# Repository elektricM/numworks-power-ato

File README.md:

# NumWorks N0100 Power Module

Custom power management board for running a Raspberry Pi Zero 2W inside a NumWorks N0100 calculator.

## Why This Exists

The [numworks-rpi](https://github.com/elektricM/numworks-rpi) project replaces the internals of a NumWorks calculator with a Raspberry Pi Zero 2W running Linux. This requires a custom power solution that can:
- ✅ Charge the Li-Ion battery (replacing the failed RT9526A charger)
- ✅ Protect the battery (overcurrent, overvoltage, undervoltage)
- ✅ Provide stable 5V power for the Raspberry Pi from a 3.7V battery
- ✅ Fit within the calculator's tight space constraints (38x24mm max)

This board does all of that in a single custom PCB.

## What It Does

**Three integrated circuits on one compact board:**

### 1. TP4056 Li-Ion Charger
Replaces the dead RT9526A charger on the original calculator. Standard 1A charge current with automatic termination.

### 2. DW01A + FS8205A Battery Protection
Complete protection circuitry:
- Overcurrent protection (discharge > 3A, charge > 1.5A)
- Overvoltage protection (> 4.25V)
- Undervoltage protection (< 2.4V)
- Auto-recovery when fault conditions clear

### 3. TPS63020 Buck-Boost Converter
Maintains stable 5V output for the Raspberry Pi across the full battery voltage range (3.0V - 4.2V):
- 95% efficiency typical
- Up to 2A output current
- Seamless transition between buck and boost modes

## Why atopile?

This board is designed with [atopile](https://atopile.io), a modern code-first PCB design tool, instead of traditional KiCad or Altium.

**Benefits:**
- 📝 **Version control friendly** — Circuit described in plain text, easy to diff and review
- 🔍 **Automatic part sourcing** — Searches JLCPCB/LCSC inventory for available parts
- 🔄 **Parametric components** — Easy to swap parts while maintaining electrical compatibility
- 🧪 **Design validation** — Catch errors before layout with built-in checking

All components are sourced from JLCPCB/LCSC for straightforward assembly and low-cost manufacturing.

## Component Selection

| Component | Part Number | Why This One |
|-----------|-------------|--------------|
| Charger IC | TP4056 | Ubiquitous, cheap (~$0.10), proven reliability, 1A charge current matches original |
| Protection IC | DW01A | Industry standard battery protection IC, tiny SOT-23-6 package |
| Protection MOSFETs | FS8205A | Dual N-channel MOSFETs in SOT-23-6, perfectly matched for DW01A |
| Buck-Boost | TPS63020 | Can operate in buck OR boost mode, 95% efficiency, up to 2A output, small footprint |

Full design rationale and power budget analysis available in [docs/design-spec.md](docs/design-spec.md).

## Board Specifications

- **Dimensions:** 38mm × 24mm (fits NumWorks internal space)
- **Input voltage:** USB 5V (charging) or battery 3.0V-4.2V (operation)
- **Output voltage:** 5.0V ± 2% (for Raspberry Pi)
- **Maximum output current:** 2A continuous (sufficient for RPi Zero 2W)
- **Charge current:** 1A (programmable via resistor)
- **Layers:** 2-layer PCB
- **Manufacturing:** Designed for JLCPCB assembly

## Status

✅ **Tested and working** — Successfully integrated into the numworks-rpi project. Powers the Raspberry Pi Zero 2W reliably with good battery life.

## Building

Requires [atopile](https://atopile.io) v0.14.0 or newer.

```bash
# Install atopile
pip install atopile

# Build the design
ato build

# Output files will be in build/
```

The build generates:
- Netlist (JSON)
- Schematic (SVG)
- Layout files for manufacturing

## Related Projects

- **[numworks-rpi](https://github.com/elektricM/numworks-rpi)** — Main project: Raspberry Pi Zero 2W running Linux inside a NumWorks calculator
- **[numworks-power-pcb](https://github.com/elektricM/numworks-power-pcb)** — Earlier KiCad-based version of this board (deprecated)

## Documentation

- **[Design Spec](docs/design-spec.md)** — Complete circuit design, pin mappings, component selection rationale, and power budget calculations
- **[Tool Learnings](docs/tool-learnings.md)** — Comparison of PCB design tools: atopile vs traditional EDA

## Project Structure

```
numworks-power-ato/
├── ato.yaml              # atopile project configuration
├── main.ato              # Top-level circuit definition
├── parts/                # Component library (charger, protection, buck-boost)
├── layouts/              # PCB layout definitions
├── docs/                 # Design documentation
│   ├── design-spec.md    # Circuit design and analysis
│   └── tool-learnings.md # PCB tool comparison
├── schematic.svg         # Generated schematic image
└── *.py                  # Build and layout automation scripts
```

## Manufacturing

This board is designed for JLCPCB's PCB assembly service:
1. Export Gerber files from atopile build output
2. Upload to JLCPCB
3. All components are in JLCPCB's parts library
4. SMT assembly is straightforward with BOM and pick-place files

## License

MIT License — see [LICENSE.txt](LICENSE.txt) for details.

---

**Part of the [numworks-rpi](https://github.com/elektricM/numworks-rpi) project**

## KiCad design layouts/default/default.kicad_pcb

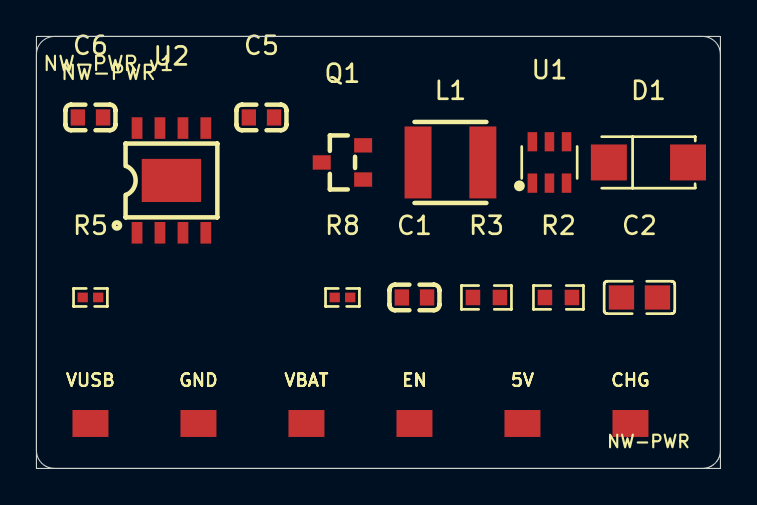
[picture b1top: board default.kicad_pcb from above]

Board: 2 copper layers, 38.0 x 24.0 mm, 19 parts (0 on the bottom side), 10 nets, no tracks yet.

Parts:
C1, C5, C6: 0F; C0603
C2: 0F; C0805
D1: SMA_L4.3-W2.6-LS5.2-RD
J1, J2, J3, J4, J5, J6: SolderPad
L1: IND-SMD_L4.0-W4.0_LQH44PN2R2MP0L
Q1: SOT-23_L2.9-W1.3-P1.90-LS2.4-BR
R2: 30000Ω; R0603
R3: 220000Ω; R0603
R5: 2000Ω; R0402
R8: 100000Ω; R0402
U1: SOT-23-6_L2.9-W1.6-P0.95-LS2.8-BL
U2: ESOP-8_L4.9-W3.9-P1.27-LS6.0-BL-EP

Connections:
2: D1.2, L1.2, U1.1
FB: R2.1, R3.2, U1.3
PROG: R5.1, U2.2
c_bat-power-hv: C5.1, J5.1, Q1.2, R8.1, U2.5
c_in-power-hv: C6.1, J6.1, U2.4, U2.8
c_out-power-hv: C2.1, D1.1, J4.1, R3.1
chg_stat: J1.1, U2.7
hv: C1.1, L1.1, Q1.3, U1.4, U1.5
lv: C1.2, C2.2, C5.2, C6.2, J2.1, R2.2, R5.2, U1.2, U2.1, U2.3, U2.9
pi_en: J3.1, Q1.1, R8.2

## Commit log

2026-02-02 NumWorks N0100 power module - atopile build (TP4056 + DW01A + TPS63020)
2026-02-02 Upgrade to atopile v0.14.0 (Python 3.14), fix pin names
2026-02-02 Rearrange PCB layout: group by functional block (buck-boost/charger/protection/monitor), add 39.5x16.5mm board outline
2026-02-02 Clean slate: remove old PCB code, keep docs (design spec + tool learnings)
2026-02-02 Fresh build: TP4056 charger + DW01A/FS8205A protection + TPS63020 buck-boost, layout grouped by block (39x17mm)
2026-02-02 Simplify: remove battery protection, add AO3401A P-MOSFET power switch for Pi (35x15mm, 19 components)
2026-02-02 Remove battery monitor (mainboard handles it), 16 components on 32x15mm
    Firmware confirmed: zardam's rpi.h uses PB9 P-channel MOSFET
    - PowerPin(GPIOB, 9), drive low = on, float = off
    - Matches our AO3401A + 100k pull-up circuit exactly
2026-02-02 Replace TPS63020 with SX1308 boost converter
    - SX1308 (C78162): SOT-23-6, 2A output, hand-solderable
    - Added SS34 Schottky diode (C8678) for async boost rectification
    - Simplified MOSFET gate: removed unnecessary R_gate to GND, keep only 100kΩ pull-up
    - Removed TPS63020 (VSON-14 pads too small for hand soldering)
    - Feedback divider: 220kΩ/30kΩ → 5.0V output
    - BOM reduced from 16 to 12 components
2026-02-02 Optimize JLCPCB cost: use 0603 feedback resistors (Basic parts)
    30kΩ and 220kΩ are Extended in 0402 but Basic in 0603.
    Saves $6 in extended part fees (from $15 to $9).
2026-02-02 Use compact 4x4x2mm inductor (SMNR4020-22UH)
    Replaced bulky 7.3x6.6x3mm inductor with 4x4x2mm shielded version.
    Same 22µH value, 1.05A rated - sufficient for Pi Zero 2W load.
    Max component height now 2.1mm (SS34 Schottky diode).
2026-02-02 Add PCB layout: 6 solder pads, component placement, routing, ground pour
    - Created SolderPad component (2x1.5mm SMD pads) for 6 wire connections
    - Board outline: 30x18mm with rounded corners
    - 3-zone layout: charger (left) → MOSFET (center) → boost (right)
    - Solder pads along bottom edge: VUSB, GND, VBAT, PI_EN, V5_PI, CHG
    - 50 trace segments, 11 vias, GND pour on B.Cu
    - Power traces 0.5mm, signal traces 0.25mm
2026-02-02 Fix layout: proper pad spacing, clean placement, remove bad routing
    - 6 solder pads evenly spaced along bottom edge (4.8mm apart)
    - Components grouped: charger left, MOSFET center, boost right
    - Removed all programmatic traces/vias/zones - route in KiCad
    - Clean silkscreen labels (VUSB, GND, VBAT, EN, 5V, CHG)
    - 30x18mm board outline
2026-02-02 Add schematic diagram SVG
2026-02-02 Regenerate schematic from atopile graph data (verified netlist)
2026-02-02 Proper schematic via netlistsvg (Yosys JSON netlist)
2026-02-02 Clean schematic: fix cell names, no duplicates
2026-02-02 Fix all 6 solder pad positions (were stacked, now spaced)
2026-02-02 Layout v2: proper spacing, 38x24mm board, GND pour, no overlaps
    - Components spaced by actual footprint size
    - 3 zones: charger (left) | MOSFET (center) | boost (right)
    - Row 1 (y=87): ICs, inductor, diode
    - Row 2 (y=95): small passives
    - Row 3 (y=101.5): 6 solder pads, 6mm apart
    - GND copper pour on B.Cu
2026-02-02 Layout v3: rounded corners, all components horizontal, proper spacing
    - 1mm rounded corners on board outline
    - All passives horizontal (no rotation surprises)
    - C6 and C5 above U2 (not overlapping)
    - R5 moved to row 2 with space
    - R2/R3 feedback divider 4mm apart (no overlap)
    - C1/C2 properly spaced in boost row 2
2026-02-02 Fix text: move refs to sides, hide values, clean NW-PWR
2026-02-06 docs: expand README with detailed component info and rationale
2026-02-20 Add CERN-OHL-S-2.0 license
